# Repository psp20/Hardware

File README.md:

# Hardware
Vier Gewinnt Hardware Repository
## Schaltplan
* [x] Komponenten festlegen
* [x] Schaltplan fertigstellen
* [x] Sanity checks durchführen
* [x] BOM erstellen
## Platinenlayout
* [x] Größe festlegen
* [x] Footprints auswählen
* [x] Trace-routing fertigstellen
## Produktion
* [x] Produktionsmöglichkeiten klären
* [ ] Prototyp bestellen

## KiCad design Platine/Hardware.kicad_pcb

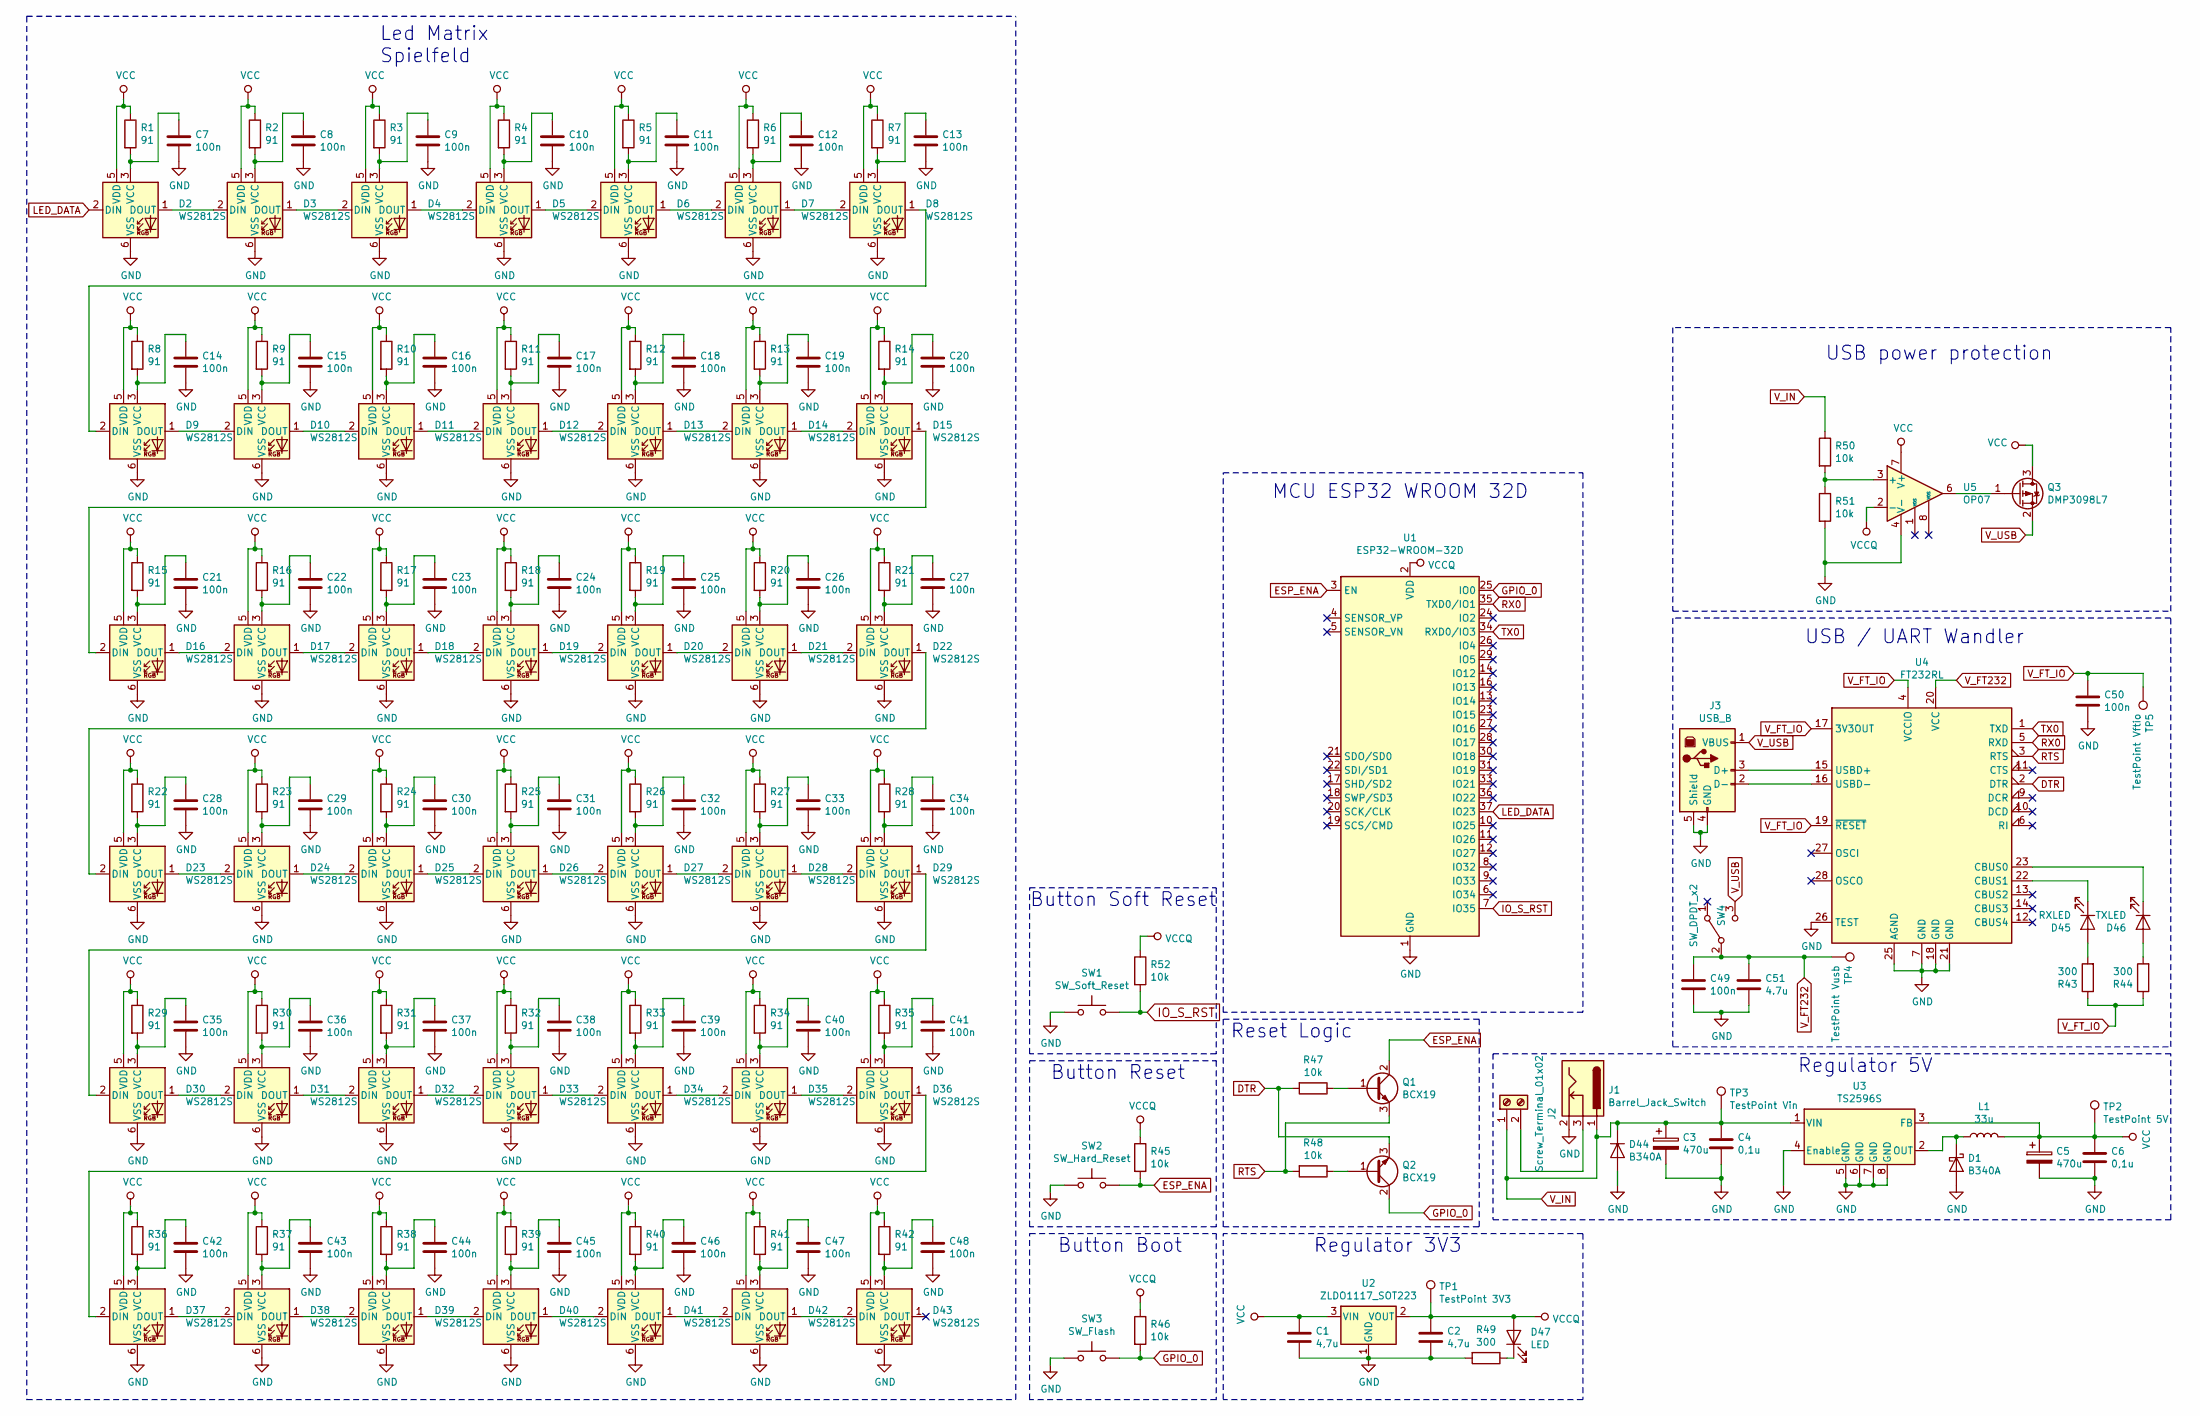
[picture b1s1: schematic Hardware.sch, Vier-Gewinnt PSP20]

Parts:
C1, C2: 4,7u; C_0805_2012Metric_Pad1.15x1.40mm_HandSolder
C3: 470u; CP_Elec_8x10
C4, C6: 0,1u; C_0805_2012Metric_Pad1.15x1.40mm_HandSolder
C5: 470u; CP_Elec_6.3x7.7
C7, C8, C9, C10, C11, C12, C13, C14, C15, C16, C17, C18, C19, C20, C21, C22, C23, C24, C25, C26, C27, C28, C29, C30, C31, C32, C33, C34, C35, C36, C37, C38, C39, C40, C41, C42, C43, C44, C45, C46, C47, C48: 100n; R_0805_2012Metric_Pad1.15x1.40mm_HandSolder
C49, C50: 100n; C_0805_2012Metric_Pad1.15x1.40mm_HandSolder
C51: 4.7u; C_0805_2012Metric_Pad1.15x1.40mm_HandSolder
D1, D44: B340A; D_SMA_Handsoldering
D2, D3, D4, D5, D6, D7, D8, D9, D10, D11, D12, D13, D14, D15, D16, D17, D18, D19, D20, D21, D22, D23, D24, D25, D26, D27, D28, D29, D30, D31, D32, D33, D34, D35, D36, D37, D38, D39, D40, D41, D42, D43: WS2812S; LED_WS2812_PLCC6_5.0x5.0mm_P1.6mm
D45: RXLED; LED_0805_2012Metric_Pad1.15x1.40mm_HandSolder
D46: TXLED; LED_0805_2012Metric_Pad1.15x1.40mm_HandSolder
D47: LED; LED_0805_2012Metric_Pad1.15x1.40mm_HandSolder
J1: Barrel_Jack_Switch; BarrelJack_BKL_072759
J2: Screw_Terminal_01x02; TerminalBlock_RND_205-00001_1x02_P5.00mm_Horizontal
J3: USB_B; USB_B_OST_USB-B1HSxx_Horizontal
L1: 33u; L_10.4x10.4_H4.8
Q1, Q2: BCX19; SOT-23
Q3: DMP3098L7; SOT-23
R1, R2, R3, R4, R5, R6, R7, R8, R9, R10, R11, R12, R13, R14, R15, R16, R17, R18, R19, R20, R21, R22, R23, R24, R25, R26, R27, R28, R29, R30, R31, R32, R33, R34, R35, R36, R37, R38, R39, R40, R41, R42: 91; R_0805_2012Metric_Pad1.15x1.40mm_HandSolder
R43, R44, R49: 300; R_0805_2012Metric_Pad1.15x1.40mm_HandSolder
R45, R46, R47, R48, R50, R51, R52: 10k; R_0805_2012Metric_Pad1.15x1.40mm_HandSolder
SW1: SW_Soft_Reset; SW_1612.11
SW2: SW_Hard_Reset; SW_1612.11
SW3: SW_Flash; SW_1612.11
SW4: SW_DPDT_x2; Switch
TP1: TestPoint 3V3; TestPoint_Pad_D2.0mm
TP2: TestPoint 5V; TestPoint_Pad_D2.0mm
TP3: TestPoint Vin; TestPoint_Pad_D2.0mm
TP4: TestPoint Vusb; TestPoint_Pad_D2.0mm
TP5: TestPoint Vftio; TestPoint_Pad_D2.0mm
U1: ESP32-WROOM-32D; ESP32-WROOM-32
U2: ZLDO1117_SOT223; SOT-223-3_TabPin2
U3: TS2596S; SOP-8_3.76x4.96mm_P1.27mm
U4: FT232RL; SSOP-28_5.3x10.2mm_P0.65mm
U5: OP07; SO-8_5.3x6.2mm_P1.27mm

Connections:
DTR: Q2.3 (E), R47.2, U4.2 (DTR)
ESP_ENA: Q1.2 (C), R45.2, SW2.2, U1.3 (EN)
GND: C1.2, C2.2, C3.2, C4.2, C5.2, C6.2, C7.1, C8.1, C9.1, C10.1, C11.1, C12.1, C13.1, C14.1, C15.1, C16.1, C17.1, C18.1, C19.1, C20.1, C21.1, C22.1, C23.1, C24.1, C25.1, C26.1, C27.1, C28.1, C29.1, C30.1, C31.1, C32.1, C33.1, C34.1, C35.1, C36.1, C37.1, C38.1, C39.1, C40.1, C41.1, C42.1, C43.1, C44.1, C45.1, C46.1, C47.1, C48.1, C49.2, C50.2, C51.2, D1.2 (A), D2.6 (VSS), D3.6 (VSS), D4.6 (VSS), D5.6 (VSS), D6.6 (VSS), D7.6 (VSS), D8.6 (VSS), D9.6 (VSS), D10.6 (VSS), D11.6 (VSS), D12.6 (VSS), D13.6 (VSS), D14.6 (VSS), D15.6 (VSS), D16.6 (VSS), D17.6 (VSS), D18.6 (VSS), D19.6 (VSS), D20.6 (VSS), D21.6 (VSS), D22.6 (VSS), D23.6 (VSS), D24.6 (VSS), D25.6 (VSS), D26.6 (VSS), D27.6 (VSS), D28.6 (VSS), D29.6 (VSS), D30.6 (VSS), D31.6 (VSS), D32.6 (VSS), D33.6 (VSS), D34.6 (VSS), D35.6 (VSS), D36.6 (VSS), D37.6 (VSS), D38.6 (VSS), D39.6 (VSS), D40.6 (VSS), D41.6 (VSS), D42.6 (VSS), D43.6 (VSS), D44.2 (A), J1.2, J3.4 (GND), J3.5 (Shield), R49.2, R51.2, SW1.1, SW2.1, SW3.1, U1.1 (GND), U1.15 (GND), U1.38 (GND), U1.39 (GND), U2.1 (GND), U3.4 (Enable), U3.5 (GND), U3.6 (GND), U3.7 (GND), U3.8 (GND), U4.7 (GND), U4.18 (GND), U4.21 (GND), U4.25 (AGND), U4.26 (TEST), U5.4 (V-)
GPIO_0: Q2.2 (C), R46.2, SW3.2, U1.25 (IO0)
IO_S_RST: R52.2, SW1.2, U1.7 (IO35)
LED_DATA: D2.2 (DIN), U1.37 (IO23)
unnamed: C7.2, D2.3 (VCC), R1.2
unnamed: C8.2, D3.3 (VCC), R2.2
unnamed: C9.2, D4.3 (VCC), R3.2
unnamed: C10.2, D5.3 (VCC), R4.2
unnamed: C11.2, D6.3 (VCC), R5.2
unnamed: C12.2, D7.3 (VCC), R6.2
unnamed: C13.2, D8.3 (VCC), R7.2
unnamed: C14.2, D9.3 (VCC), R8.2
unnamed: C15.2, D10.3 (VCC), R9.2
unnamed: C16.2, D11.3 (VCC), R10.2
unnamed: C17.2, D12.3 (VCC), R11.2
unnamed: C18.2, D13.3 (VCC), R12.2
unnamed: C19.2, D14.3 (VCC), R13.2
unnamed: C20.2, D15.3 (VCC), R14.2
unnamed: C21.2, D16.3 (VCC), R15.2
unnamed: C22.2, D17.3 (VCC), R16.2
unnamed: C23.2, D18.3 (VCC), R17.2
unnamed: C24.2, D19.3 (VCC), R18.2
unnamed: C25.2, D20.3 (VCC), R19.2
unnamed: C26.2, D21.3 (VCC), R20.2
unnamed: C27.2, D22.3 (VCC), R21.2
unnamed: C28.2, D23.3 (VCC), R22.2
unnamed: C29.2, D24.3 (VCC), R23.2
unnamed: C30.2, D25.3 (VCC), R24.2
unnamed: C31.2, D26.3 (VCC), R25.2
unnamed: C32.2, D27.3 (VCC), R26.2
unnamed: C33.2, D28.3 (VCC), R27.2
unnamed: C34.2, D29.3 (VCC), R28.2
unnamed: C35.2, D30.3 (VCC), R29.2
unnamed: C36.2, D31.3 (VCC), R30.2
unnamed: C37.2, D32.3 (VCC), R31.2
unnamed: C38.2, D33.3 (VCC), R32.2
unnamed: C39.2, D34.3 (VCC), R33.2
unnamed: C40.2, D35.3 (VCC), R34.2
unnamed: C41.2, D36.3 (VCC), R35.2
unnamed: C42.2, D37.3 (VCC), R36.2
unnamed: C43.2, D38.3 (VCC), R37.2
unnamed: C44.2, D39.3 (VCC), R38.2
unnamed: C45.2, D40.3 (VCC), R39.2
unnamed: C46.2, D41.3 (VCC), R40.2
unnamed: C47.2, D42.3 (VCC), R41.2
unnamed: C48.2, D43.3 (VCC), R42.2
unnamed: D1.1 (K), L1.1, U3.2 (OUT)
unnamed: D2.1 (DOUT), D3.2 (DIN)
unnamed: D3.1 (DOUT), D4.2 (DIN)
unnamed: D4.1 (DOUT), D5.2 (DIN)
unnamed: D5.1 (DOUT), D6.2 (DIN)
unnamed: D6.1 (DOUT), D7.2 (DIN)
unnamed: D7.1 (DOUT), D8.2 (DIN)
unnamed: D8.1 (DOUT), D9.2 (DIN)
unnamed: D10.1 (DOUT), D11.2 (DIN)
unnamed: D9.1 (DOUT), D10.2 (DIN)
unnamed: D11.1 (DOUT), D12.2 (DIN)
unnamed: D12.1 (DOUT), D13.2 (DIN)
unnamed: D13.1 (DOUT), D14.2 (DIN)
unnamed: D14.1 (DOUT), D15.2 (DIN)
unnamed: D15.1 (DOUT), D16.2 (DIN)
unnamed: D16.1 (DOUT), D17.2 (DIN)
unnamed: D17.1 (DOUT), D18.2 (DIN)
unnamed: D18.1 (DOUT), D19.2 (DIN)
unnamed: D19.1 (DOUT), D20.2 (DIN)
unnamed: D20.1 (DOUT), D21.2 (DIN)
unnamed: D21.1 (DOUT), D22.2 (DIN)
unnamed: D22.1 (DOUT), D23.2 (DIN)
unnamed: D23.1 (DOUT), D24.2 (DIN)
unnamed: D24.1 (DOUT), D25.2 (DIN)
unnamed: D25.1 (DOUT), D26.2 (DIN)
unnamed: D26.1 (DOUT), D27.2 (DIN)
unnamed: D27.1 (DOUT), D28.2 (DIN)
unnamed: D28.1 (DOUT), D29.2 (DIN)
unnamed: D29.1 (DOUT), D30.2 (DIN)
unnamed: D30.1 (DOUT), D31.2 (DIN)
unnamed: D31.1 (DOUT), D32.2 (DIN)
unnamed: D32.1 (DOUT), D33.2 (DIN)
unnamed: D33.1 (DOUT), D34.2 (DIN)
unnamed: D34.1 (DOUT), D35.2 (DIN)
unnamed: D35.1 (DOUT), D36.2 (DIN)
unnamed: D36.1 (DOUT), D37.2 (DIN)
unnamed: D37.1 (DOUT), D38.2 (DIN)
unnamed: D38.1 (DOUT), D39.2 (DIN)
unnamed: D39.1 (DOUT), D40.2 (DIN)
unnamed: D40.1 (DOUT), D41.2 (DIN)
unnamed: D41.1 (DOUT), D42.2 (DIN)
unnamed: D42.1 (DOUT), D43.2 (DIN)
unnamed: D45.1 (K), U4.22 (CBUS1)
unnamed: D45.2 (A), R43.2
unnamed: D46.1 (K), U4.23 (CBUS0)
unnamed: D46.2 (A), R44.2
unnamed: D47.1 (K), R49.1
unnamed: J1.3, J2.2
unnamed: J3.2 (D-), U4.16 (USBD-)
unnamed: J3.3 (D+), U4.15 (USBD+)
unnamed: Q1.1 (B), R47.1
unnamed: Q2.1 (B), R48.1
unnamed: Q3.1 (Gate), U5.6
unnamed: R50.2, R51.1, U5.3 (+)
RTS: Q1.3 (E), R48.2, U4.3 (RTS)
RX0: U1.35 (TXD0/IO1), U4.5 (RXD)
TX0: U1.34 (RXD0/IO3), U4.1 (TXD)
VCC: C1.1, C5.1, C6.1, D2.5 (VDD), D3.5 (VDD), D4.5 (VDD), D5.5 (VDD), D6.5 (VDD), D7.5 (VDD), D8.5 (VDD), D9.5 (VDD), D10.5 (VDD), D11.5 (VDD), D12.5 (VDD), D13.5 (VDD), D14.5 (VDD), D15.5 (VDD), D16.5 (VDD), D17.5 (VDD), D18.5 (VDD), D19.5 (VDD), D20.5 (VDD), D21.5 (VDD), D22.5 (VDD), D23.5 (VDD), D24.5 (VDD), D25.5 (VDD), D26.5 (VDD), D27.5 (VDD), D28.5 (VDD), D29.5 (VDD), D30.5 (VDD), D31.5 (VDD), D32.5 (VDD), D33.5 (VDD), D34.5 (VDD), D35.5 (VDD), D36.5 (VDD), D37.5 (VDD), D38.5 (VDD), D39.5 (VDD), D40.5 (VDD), D41.5 (VDD), D42.5 (VDD), D43.5 (VDD), L1.2, Q3.3 (Drain), R1.1, R2.1, R3.1, R4.1, R5.1, R6.1, R7.1, R8.1, R9.1, R10.1, R11.1, R12.1, R13.1, R14.1, R15.1, R16.1, R17.1, R18.1, R19.1, R20.1, R21.1, R22.1, R23.1, R24.1, R25.1, R26.1, R27.1, R28.1, R29.1, R30.1, R31.1, R32.1, R33.1, R34.1, R35.1, R36.1, R37.1, R38.1, R39.1, R40.1, R41.1, R42.1, TP2.1, U2.3 (VIN), U3.3 (FB), U5.7 (V+)
VCCQ: C2.1, D47.2 (A), R45.1, R46.1, R52.1, TP1.1, U1.2 (VDD), U2.2 (VOUT), U5.2 (-)
V_FT232: C49.1, C51.1, SW4.2 (B), TP4.1, U4.20 (VCC)
V_FT_IO: C50.1, R43.1, R44.1, TP5.1, U4.4 (VCCIO), U4.17 (3V3OUT), U4.19 (~RESET~)
V_IN: C3.1, C4.1, D44.1 (K), J1.1, J2.1, R50.1, TP3.1, U3.1 (VIN)
V_USB: J3.1 (VBUS), Q3.2 (Source), SW4.3 (C)

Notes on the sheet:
Regulator 3V3
Regulator 5V
Led Matrix Spielfeld
Reset Logic
USB / UART Wandler
Button Boot
Button Reset
Button Soft Reset
MCU ESP32 WROOM 32D
USB power protection

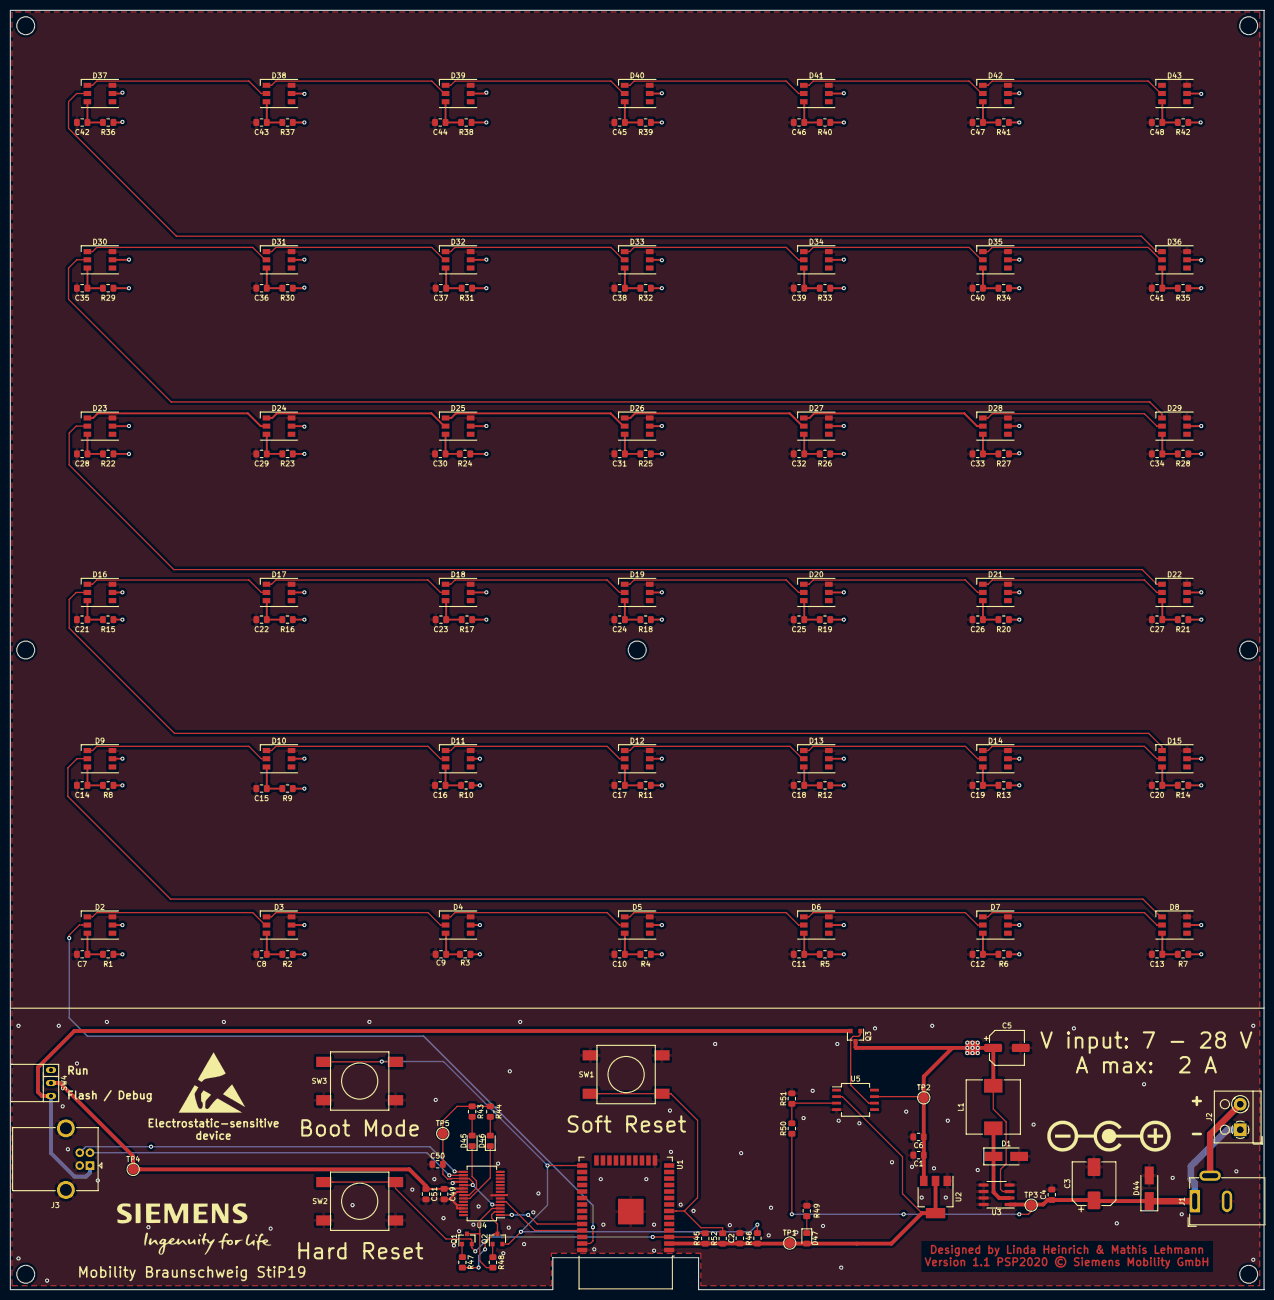
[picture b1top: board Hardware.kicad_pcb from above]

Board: 2 copper layers, 245.0 x 250.0 mm, 171 parts (0 on the bottom side), 111 nets.

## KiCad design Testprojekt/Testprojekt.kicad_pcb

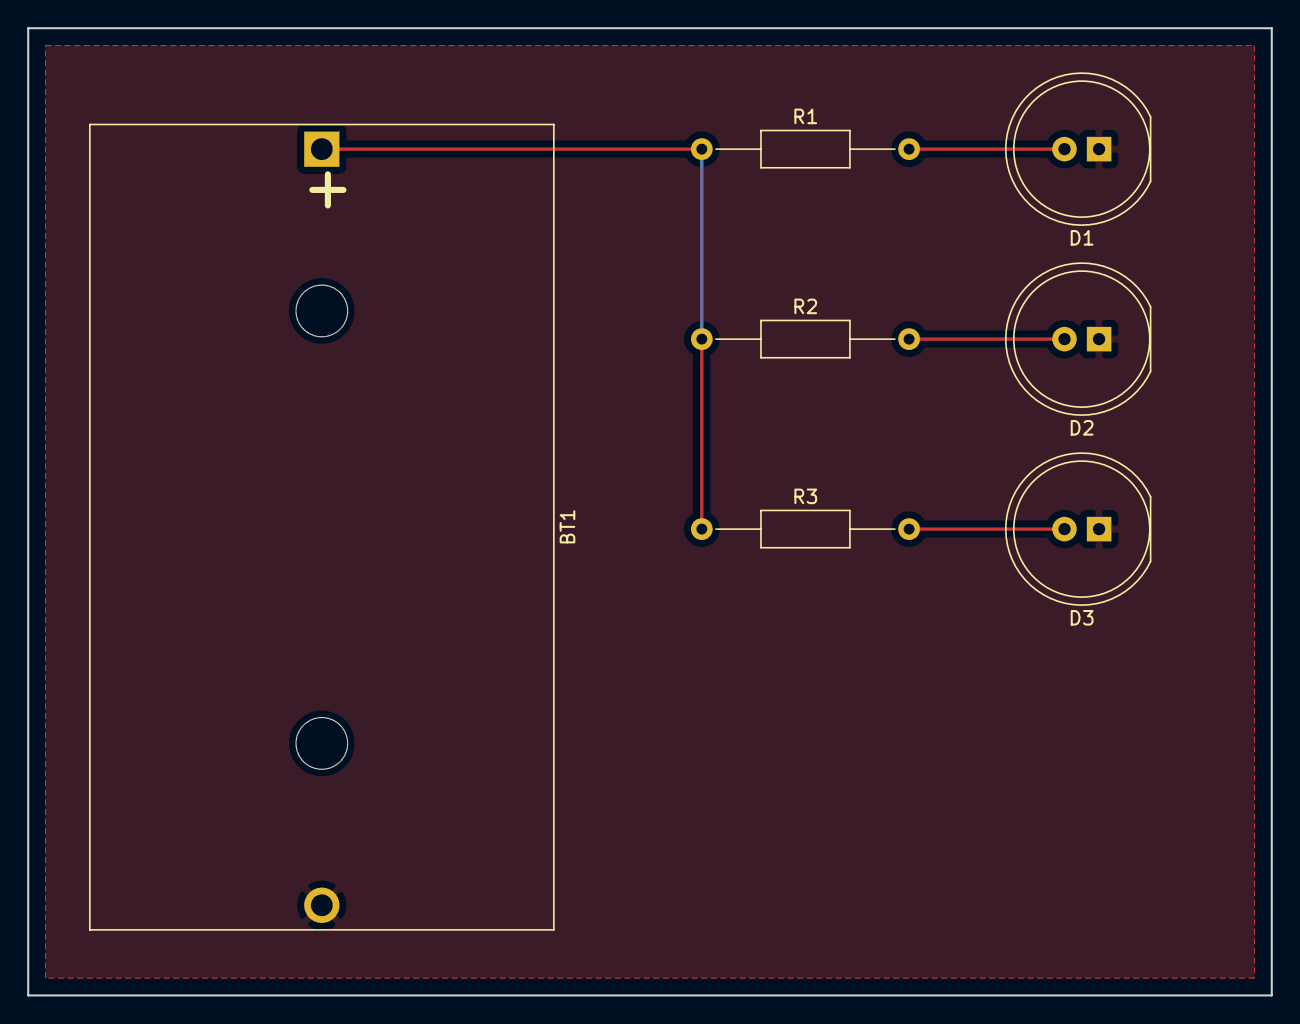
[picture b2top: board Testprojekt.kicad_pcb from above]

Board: 2 copper layers, 91.4 x 71.1 mm, 7 parts (0 on the bottom side), 5 nets.

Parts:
BT1: Battery; BatteryHolder_Bulgin_BX0036_1xC
D1, D2, D3: LED; LED_D10.0mm
R1, R2, R3: 200; R_Axial_DIN0207_L6.3mm_D2.5mm_P15.24mm_Horizontal

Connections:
unnamed: BT1.1, R1.1, R2.1, R3.1
unnamed: BT1.2, D1.1, D2.1, D3.1
unnamed: D1.2, R1.2
unnamed: D2.2, R2.2
unnamed: D3.2, R3.2

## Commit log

2020-11-09 Created test project to teach workflow s Please enter the commit message for your changes. Lines starting
2020-11-09 Testprojekt Platinendesign erstellt
2020-11-17 Started schematic
2020-11-17 Spannungsregler hinzugfügt
2020-11-17 Elkos ausgewählt
2020-11-18 Erweiterung der Bauteilinformationen
2020-11-18 Finished LED Matrix Added part datasheets Updated BOM
2020-11-18 LED-Matrix Baueilnummerierung hinzugefügt und BOM erweitert
2020-11-19 Finished revision V1.0 Updated power supply input
2020-11-26 Added HAL Code
2020-11-30 Added LED matrix spaceing Added Soft-Reset Added Hard-Reset Added USB-Interface Added Programming-Button Added ISP-Programmer Created 3D Frontplate mockup
2020-11-30 Added additional 3D file formats
2020-11-30 Updated Schematic to be more intuitive to read Updated BOM
2020-12-01 Added Enclosure plan
2020-12-02 update prebuild script
2020-12-02 add prebuild script
2020-12-02 add Readme
2020-12-02 copy once
2020-12-02 remove HAL
2020-12-02 Finished PCB Layout V1 Updated Inductor for ripple reduction Rerouted FT232RL traces Added reset logic for ISP programming Added Silkscreen button labels
2020-12-02 Gehäuse Vorderseite erster Entwurf
2020-12-03 Finished review of Layout Reviewed BOM Added input cutoff form screw terminal when barreljack is used Added branding Added revision Added author Optimised routing Added screw holes for case Updated b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
2020-12-03 Updated documentation Added datasheet for terminal block Updated BOM
2020-12-05 Gehäause Vorder- und Rückseite und Taster erstellt
2020-12-07 Added 3D models for PCB preview rendering Updated Layput with 3D Models
2020-12-07 Added rendered images to documentation Deleted temporary 3D File
2020-12-07 Gehäuse fertig
2020-12-08 .stl Datei des Gehäuses erstellt
2020-12-12 einzelne stl-Dateien erstellt, Höhenunterschied der Taster beseitigt
2020-12-14 Added urgent features requested by client Added power LED Added option to supply complete PCB via USB port
2020-12-15 Production readiness Improved reverse USB powerprotection Added part orderlist
2020-12-16 Loch für Schalter und Power-LED zum Gehäuse hinzugefügt
2020-12-16 Finished Layout V1 Created Gerber and Excellion drill files Updated BOM Added order manual Added orderlist Updated Schematic
2021-01-28 Verkleinerung der Taster, Schrift auf die Gehäusefront verschoben, kleine Anpassungen
2021-02-18 Aussparung der Platine im Gehäuse vergrößert
2021-02-24 Fixed RX & TX Issue #5 Switched RX & TX of FT232RL and ESP 32.
2021-02-24 Resolved Issue 6 & Issue 7 Switched Pin 2 & 3 of P-FET (Issue 6) Upgraded P-FET to handle 2A continuous (Issue 7)
2021-02-24 Rerouted feedbackline. close #4 Rerouted to after smoothing coil
2021-02-24 Added Info to silkscreen Polarity info added. close #10, close #3 Added ESD warning Changed revision marker to V1.1 Added switch labeling
2021-02-24 Added Pullup and conneced floating GND peninsulas Added 10k pullup on Soft Rest button (close #9) Via'd GND peninsulas to GND to prevent oscillation
2021-02-24 Isolated ZLDO tab from GND Isolated ZLDO 1733 tab from GND (close #2)
2021-02-24 Switched input smoothing cap to 35V rated cap Switched C3 to 35V rated electrolytic capacitor (close #1)
2021-02-24 Updated BOM to match PCB Rev V1.1
2021-02-26 Riskoanalyse Überstrom-/ Überspannung
2021-03-02 weitere Anpassungen am Gehäuse
2021-03-02 Umbenennen der stl-Datei Taster und Entfernen von veralteten Versionen
2021-03-02 Finished risk analysis
2021-04-06 Added Documentation Updated libary references for KiCad

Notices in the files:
Platine/Hardware.kicad_pcb:
Version 1.1 PSP2020 © Siemens Mobility GmbH
